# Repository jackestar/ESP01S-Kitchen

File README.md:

<div align="center">
<h3>ESP01S controlled for a Resistive Element (Kitchen)</h3>

</div>

---

## Goal

Controlling a resistive AC heating element using an SSR (Solid State Relay) controlled by a ESP01 (or ESP01S, ESP8266 based board), using the ESP8266 RTOS SDK.

* Push-button On/Off :heavy_check_mark:
* App Control (On/Off, Timer, Dimmer) :heavy_check_mark:
* OTA Update :x:
* Translations :x:
* CI/CD (Github Actions) :heavy_check_mark:

## Build

> [!NOTE]
> The main difference between the ESP01 and the ESP01S is the flash memory size, the Espressif SDK allows a minimum of 1MB so it verifies that the compiled file fits in the flash memory (~450kB ~330Kb compressed).

* Install the [ESP8266 RTOS SDK](https://github.com/espressif/ESP8266_RTOS_SDK) and configure it.
* Clone this repo

```bash
git clone https://github.com/jackestar/ESP01S-Kitchen.git --depth 2
```

* set the environment `export IDF_PATH=[your ESP8266 SDK path]` and `. $IDF_PATH/export.sh`

* make and flash

```
make flash
```

## Board and Schematics

[Articulo del Esquemático](https://jackestar.netlify.app/Blog/Kicad/ESP01S-Kitchen-Driver.html)

[Kicad Project](Kicad)

# License

**This Repo** - MIT License

**ESP8266 RTOS SDK** - Apache 2.0

**Material Symbols / Material Icons** - Apache 2.0

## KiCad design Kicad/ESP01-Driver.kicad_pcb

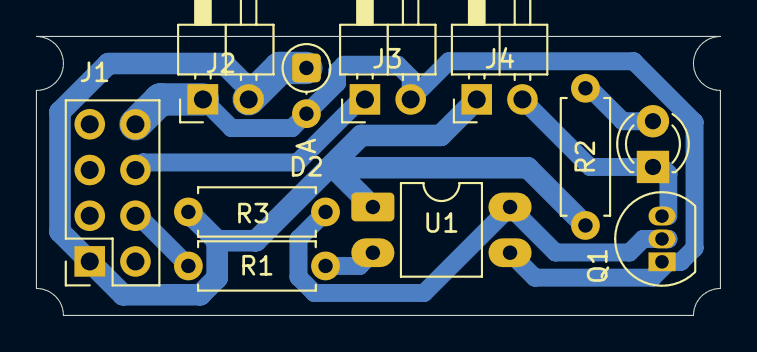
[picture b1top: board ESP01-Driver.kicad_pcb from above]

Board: 2 copper layers, 38.0 x 15.5 mm, 11 parts (0 on the bottom side), 8 nets.

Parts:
D1: LED; LED_D3.0mm
D2: 3v6; D_DO-35_SOD27_P2.54mm_Vertical_AnodeUp
J1: ESP01S; PinSocket_2x04_P2.54mm_Vertical
J2: Supply; PinHeader_1x02_P2.54mm_Horizontal
J3: Push Button; PinHeader_1x02_P2.54mm_Horizontal
J4: Relay; PinHeader_1x02_P2.54mm_Horizontal
Q1: 2N2222A; TO-92_Inline
R1: 100; R_Axial_DIN0207_L6.3mm_D2.5mm_P7.62mm_Horizontal
R2: 220; R_Axial_DIN0207_L6.3mm_D2.5mm_P7.62mm_Horizontal
R3: 3.3k; R_Axial_DIN0207_L6.3mm_D2.5mm_P7.62mm_Horizontal
U1: PC123; DIP-4_W7.62mm_LongPads

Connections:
+3V3: D2.1 (K), J1.1, J2.2, J4.1, R2.1, R3.1, U1.1
GND: D2.2 (A), J1.8, J2.1, J3.2, Q1.1 (E), U1.3
IO0: J1.4, R1.1
IO2: J1.6, J3.1
unnamed: D1.2 (A), R2.2
unnamed: D1.1 (K), J4.2, Q1.3 (C)
unnamed: Q1.2 (B), R3.2, U1.4
unnamed: R1.2, U1.2

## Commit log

2025-08-10 Working Toggle H/S
2025-08-10 Clean
2025-08-12 Beta 1
2025-08-13 Beta 1 - Base Line (UI) Some sdkconfig pr mods
2025-08-13 Beta 2 (Release Candidate) New UI
2025-08-25 Beta 2 get state
2025-08-26 Update UI/UX Add +-10 min Button Upd each 1s fix Upd Readme Add Licence Upd sdkconfig (nothing to do)
2025-08-26 Upd Github Action
2025-08-26 skdconfig with UART (for no pathed version)
2025-08-27 Add Kicad Board Schematics Upd Preview Add Build Readme Upd Github action CI
2025-08-27 Github Action Test
2025-08-27 Another Github Action Test
2025-08-27 Fix Tag problem from Github Action
2025-08-27 One Last TIme Github Action Fix
2025-08-28 CI from own github action Update Readme
2025-08-28 Make and dont size it
